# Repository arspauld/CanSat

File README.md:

## Welcome to GitHub Pages

You can use the [editor on GitHub](https://github.com/arspauld/CanSat/edit/master/README.md) to maintain and preview the content for your website in Markdown files.

Whenever you commit to this repository, GitHub Pages will run [Jekyll](https://jekyllrb.com/) to rebuild the pages in your site, from the content in your Markdown files.

### Markdown

Markdown is a lightweight and easy-to-use syntax for styling your writing. It includes conventions for

```markdown
Syntax highlighted code block

# Header 1
## Header 2
### Header 3

- Bulleted
- List

1. Numbered
2. List

**Bold** and _Italic_ and `Code` text

[Link](url) and 
```

For more details see [GitHub Flavored Markdown](https://guides.github.com/features/mastering-markdown/).

### Jekyll Themes

Your Pages site will use the layout and styles from the Jekyll theme you have selected in your [repository settings](https://github.com/arspauld/CanSat/settings). The name of this theme is saved in the Jekyll `_config.yml` configuration file.

### Support or Contact

Having trouble with Pages? Check out our [documentation](https://help.github.com/categories/github-pages-basics/) or [contact support](https://github.com/contact) and we’ll help you sort it out.

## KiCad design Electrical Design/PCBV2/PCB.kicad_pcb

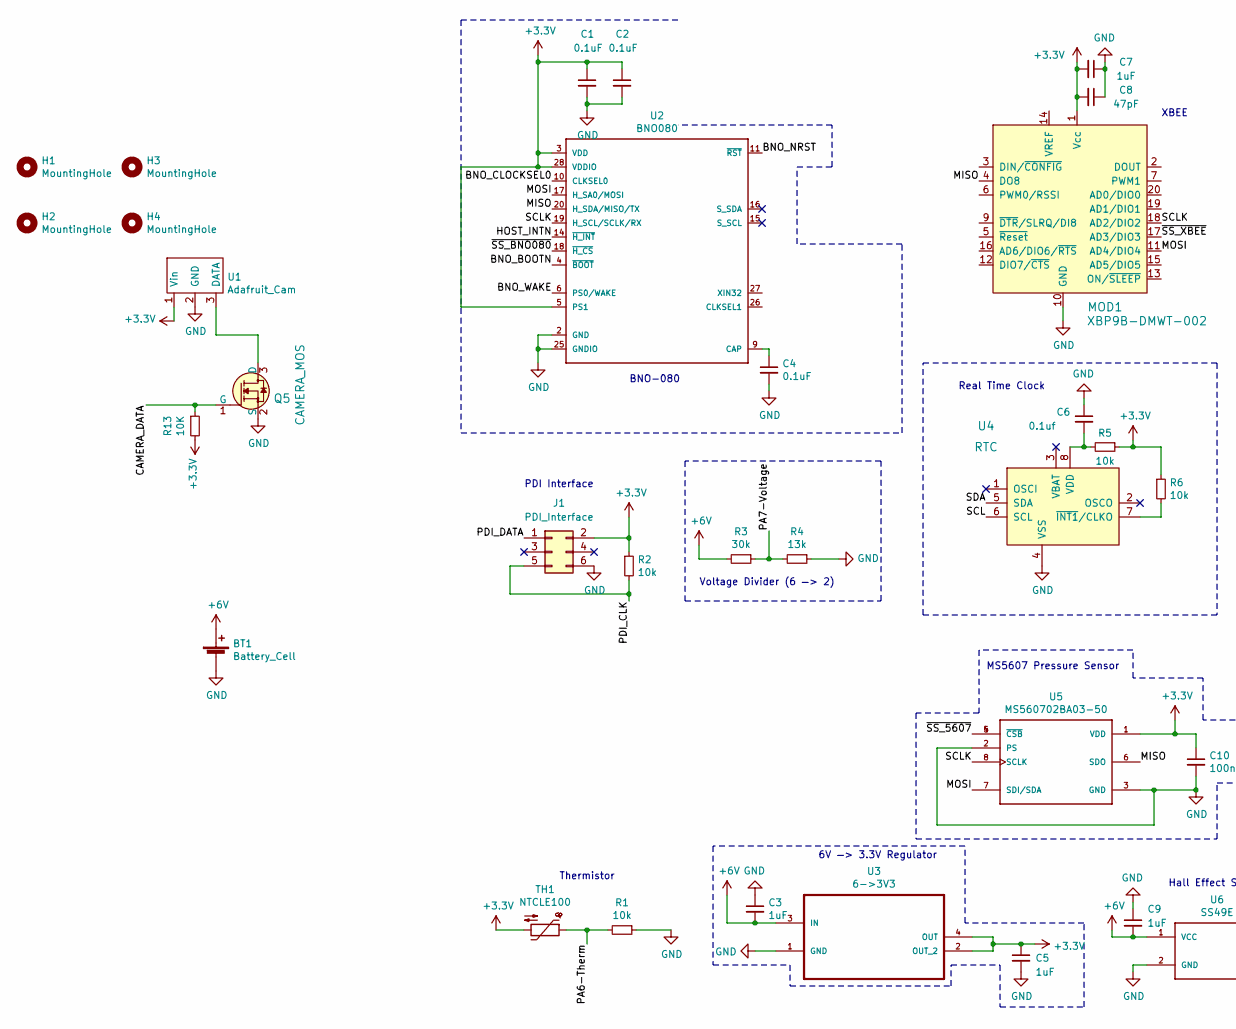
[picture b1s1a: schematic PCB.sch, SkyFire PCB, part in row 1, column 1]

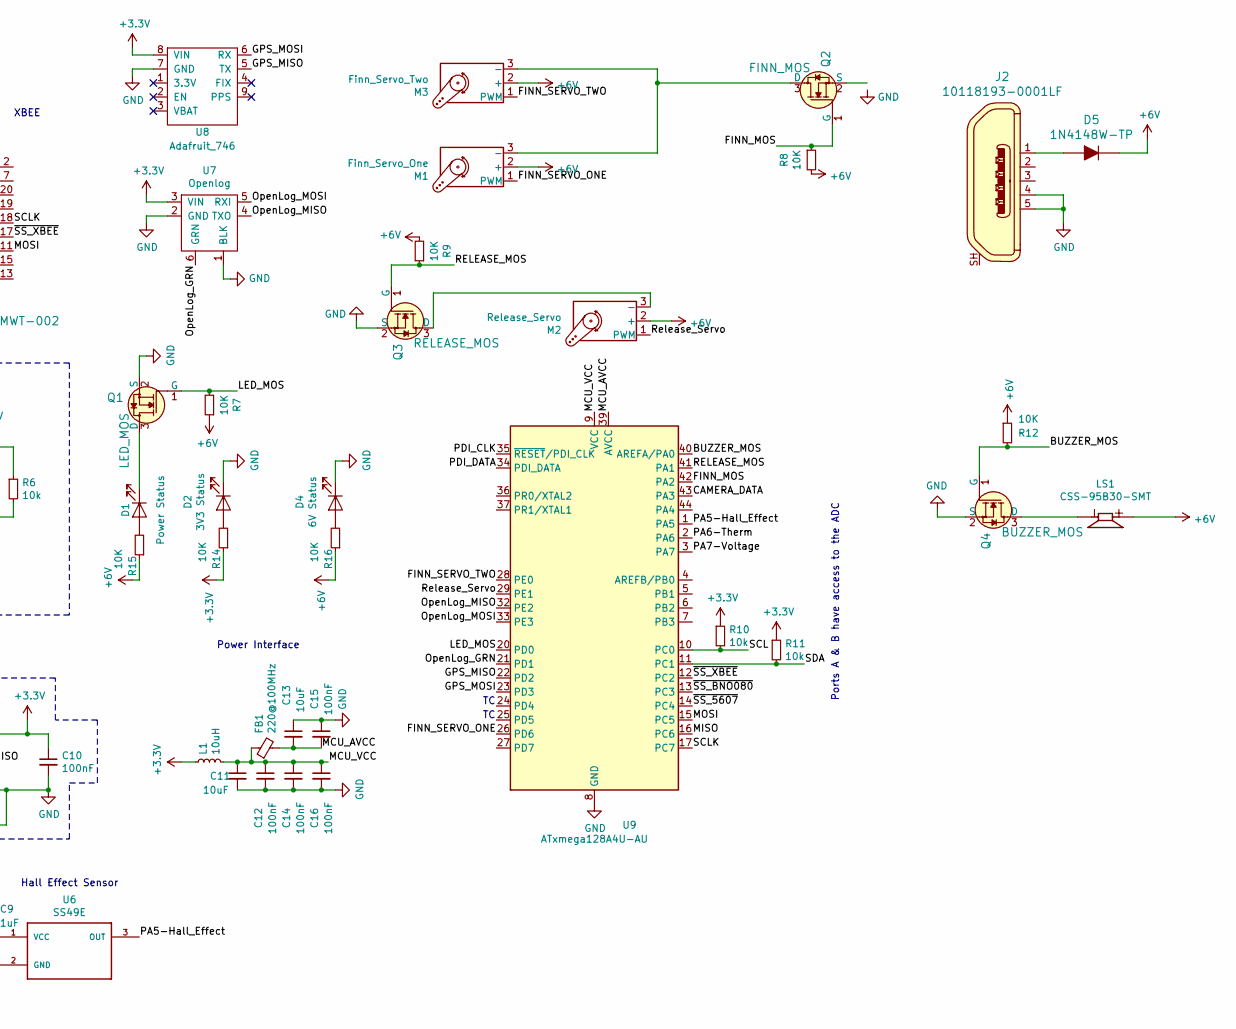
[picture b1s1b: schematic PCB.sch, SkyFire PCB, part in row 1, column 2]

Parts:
BT1: Battery_Cell; MOLEX-1X2_LOCK
C1, C2, C4: 0.1uF; C_0805_2012Metric_Pad1.15x1.40mm_HandSolder
C3, C5, C7, C9: 1uF; C_0805_2012Metric_Pad1.15x1.40mm_HandSolder
C6: 0.1uf; C_0805_2012Metric_Pad1.15x1.40mm_HandSolder
C8: 47pF; C_0805_2012Metric_Pad1.15x1.40mm_HandSolder
C10, C12, C14, C15, C16: 100nF; C_0805_2012Metric_Pad1.15x1.40mm_HandSolder
C11, C13: 10uF; C_0805_2012Metric_Pad1.15x1.40mm_HandSolder
D1: Power Status; LED_0603_1608Metric_Pad1.05x0.95mm_HandSolder
D2: 3V3 Status; LED_0603_1608Metric_Pad1.05x0.95mm_HandSolder
D4: 6V Status; LED_0603_1608Metric_Pad1.05x0.95mm_HandSolder
D5: 1N4148W-TP; SOD-123; MPN 1N4148W-TP; Digi-Key_PN 1N4148WTPMSCT-ND
FB1: 220@100MHz; L_0805_2012Metric_Pad1.15x1.40mm_HandSolder
H1, H2, H3, H4: MountingHole; MountingHole_3.2mm_M3
J1: PDI_Interface; 2X3
J2: 10118193-0001LF; USB_Micro_B_Female_10118193-0001LF; MPN 10118193-0001LF; Digi-Key_PN 609-4616-1-ND
L1: 10uH; L_0805_2012Metric_Pad1.15x1.40mm_HandSolder
LS1: CSS-95B30-SMT; CUI_CSS-95B30-SMT
M1: Finn_Servo_One; MOLEX-1X3_LOCK
M2: Release_Servo; MOLEX-1X3_LOCK
M3: Finn_Servo_Two; MOLEX-1X3_LOCK
MOD1: XBP9B-DMWT-002; XBEE_PRO-20_THT; MPN XBP9B-DMWT-002; Digi-Key_PN 602-1301-ND
Q1: LED_MOS; SOT-23-3; MPN 2N7002K-T1-E3; Digi-Key_PN 2N7002K-T1-E3CT-ND
Q2: FINN_MOS; SOT-23-3; MPN 2N7002K-T1-E3; Digi-Key_PN 2N7002K-T1-E3CT-ND
Q3: RELEASE_MOS; SOT-23-3; MPN 2N7002K-T1-E3; Digi-Key_PN 2N7002K-T1-E3CT-ND
Q4: BUZZER_MOS; SOT-23-3; MPN 2N7002K-T1-E3; Digi-Key_PN 2N7002K-T1-E3CT-ND
Q5: CAMERA_MOS; SOT-23-3; MPN 2N7002K-T1-E3; Digi-Key_PN 2N7002K-T1-E3CT-ND
R1, R2, R5, R6, R10, R11: 10k; R_0805_2012Metric_Pad1.15x1.40mm_HandSolder
R3: 30k; R_0805_2012Metric_Pad1.15x1.40mm_HandSolder
R4: 13k; R_0805_2012Metric_Pad1.15x1.40mm_HandSolder
R7, R8, R9, R12, R13, R14, R15, R16: 10K; R_0805_2012Metric_Pad1.15x1.40mm_HandSolder
TH1: NTCLE100; CP_Radial_D4.0mm_P1.50mm
U1: Adafruit_Cam; MOLEX-1X3_LOCK
U2: BNO080; LGA-28
U3: 6->3V3; SOT230P700X180-4N
U4: RTC; SOIC-8_W3.9mm; MPN PCF8523T/1,118; Digi-Key_PN 568-5306-1-ND
U5: MS560702BA03-50; SON125P300X500X100-8N
U6: SS49E; MOLEX-1X3_LOCK
U7: Openlog; 1X06
U8: Adafruit_746; 1X09
U9: ATxmega128A4U-AU; TQFP-44_10x10mm_P0.8mm

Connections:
+3V3: C1.1, C2.1, C5.1, C7.2, C8.2, C10.1, J1.2, L1.1, MOD1.1 (Vcc), R2.1, R5.1, R6.1, R10.1, R11.1, R13.2, R14.1, TH1.2, U1.1 (Vin), U2.3 (VDD), U2.5 (PS1), U2.28 (VDDIO), U3.2 (OUT_2), U3.4 (OUT), U5.1 (VDD), U7.3 (VIN), U8.8 (VIN)
+6V: BT1.1 (+), C3.2, C9.2, D5.K, LS1.P, M1.2 (+), M2.2 (+), M3.2 (+), R3.2, R7.1, R8.2, R9.2, R12.1, R15.1, R16.1, U3.3 (IN), U6.1 (VCC)
/BNO_BOOTN: U2.4 (~BOOT~)
/BNO_CLOCKSEL0: U2.10 (CLKSEL0)
/BNO_NRST: U2.11 (~RST~)
/BNO_WAKE: U2.6 (PS0/WAKE)
/BUZZER_MOS: Q4.1 (G), R12.2, U9.40 (AREFA/PA0)
/CAMERA_DATA: Q5.1 (G), R13.1, U9.43 (PA3)
/FINN_MOS: Q2.1 (G), R8.1, U9.42 (PA2)
/FINN_SERVO_ONE: M1.1 (PWM), U9.26 (PD6)
/FINN_SERVO_TWO: M3.1 (PWM), U9.28 (PE0)
/GPS_MISO: U8.5 (TX), U9.22 (PD2)
/GPS_MOSI: U8.6 (RX), U9.23 (PD3)
/HOST_INTN: U2.14 (~H_INT~)
/LED_MOS: Q1.1 (G), R7.2, U9.20 (PD0)
/MCU_AVCC: C13.2, C15.2, FB1.2, U9.39 (AVCC)
/MCU_VCC: C11.1, C12.1, C14.1, C16.1, FB1.1, L1.2, U9.9 (VCC), U9.19 (VCC), U9.31 (VCC)
/MISO: MOD1.4 (DO8), U2.20 (H_SDA/MISO/TX), U5.6 (SDO), U9.16 (PC6)
/MOSI: MOD1.11 (AD4/DIO4), U2.17 (H_SA0/MOSI), U5.7 (SDI/SDA), U9.15 (PC5)
/OpenLog_GRN: U7.6 (GRN), U9.21 (PD1)
/OpenLog_MISO: U7.4 (TXO), U9.32 (PE2)
/OpenLog_MOSI: U7.5 (RXI), U9.33 (PE3)
/PA5-Hall_Effect: U6.3 (OUT), U9.1 (PA5)
/PA6-Therm: R1.2, TH1.1, U9.2 (PA6)
/PA7-Voltage: R3.1, R4.2, U9.3 (PA7)
/PDI_CLK: J1.5, R2.2, U9.35 (~RESET~/PDI_CLK)
/PDI_DATA: J1.1, U9.34 (PDI_DATA)
/RELEASE_MOS: Q3.1 (G), R9.1, U9.41 (PA1)
/Release_Servo: M2.1 (PWM), U9.29 (PE1)
/SCL: R10.2, U4.6 (SCL), U9.10 (PC0)
/SCLK: MOD1.18 (AD2/DIO2), U2.19 (H_SCL/SCLK/RX), U5.8 (SCLK), U9.17 (PC7)
/SDA: R11.2, U4.5 (SDA), U9.11 (PC1)
/~SS_5607: U5.4 (~CSB~), U5.5 (~CSB~), U9.14 (PC4)
/~SS_BNO080: U2.18 (~H_CS~), U9.13 (PC3)
/~SS_XBEE: MOD1.17 (AD3/DIO3), U9.12 (PC2)
GND: BT1.2 (-), C1.2, C2.2, C3.1, C4.2, C5.2, C6.1, C7.1, C8.1, C9.1, C10.2, C11.2, C12.2, C13.1, C14.2, C15.1, C16.2, D2.1 (K), D4.1 (K), J1.6, J2.4, J2.5, MOD1.10 (GND), Q1.2 (S), Q3.2 (S), Q4.2 (S), Q5.2 (S), R1.1, R4.1, U1.2 (GND), U2.2 (GND), U2.25 (GNDIO), U3.1 (GND), U4.4 (VSS), U5.2 (PS), U5.3 (GND), U6.2 (GND), U7.1 (BLK), U7.2 (GND), U8.7 (GND), U9.8 (GND), U9.18 (GND), U9.30 (GND), U9.38 (GND)
unnamed: C4.1, U2.9 (CAP)
unnamed: C6.2, R5.2, U4.8 (VDD)
unnamed: D1.1 (K), Q1.3 (D)
unnamed: D1.2 (A), R15.2
unnamed: D2.2 (A), R14.2
unnamed: D4.2 (A), R16.2
unnamed: D5.A, J2.1
unnamed: LS1.N, Q4.3 (D)
unnamed: M1.3 (-), M3.3 (-), Q2.3 (D)
unnamed: M2.3 (-), Q3.3 (D)
unnamed: Q5.3 (D), U1.3 (DATA)
unnamed: R6.2, U4.7 (~INT1~/CLKO)

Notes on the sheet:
Ports A & B have access to the ADC
Voltage Divider (6 —> 2)
MS5607 Pressure Sensor
Power Interface
Hall Effect Sensor
6V —> 3.3V Regulator
PDI Interface
BNO-080
Thermistor
Real Time Clock
XBEE

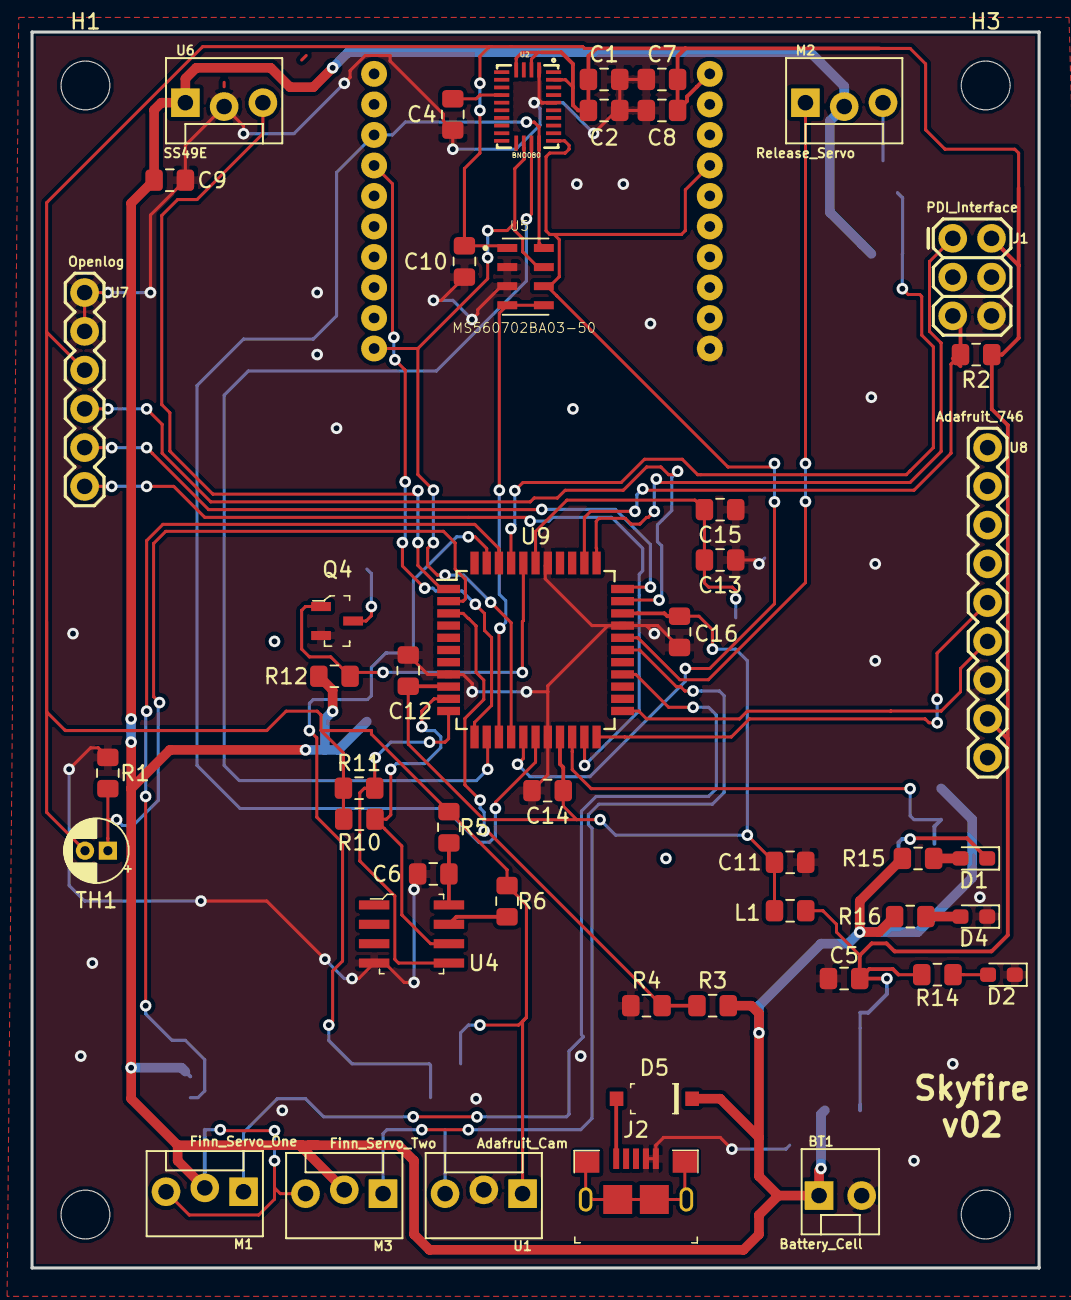
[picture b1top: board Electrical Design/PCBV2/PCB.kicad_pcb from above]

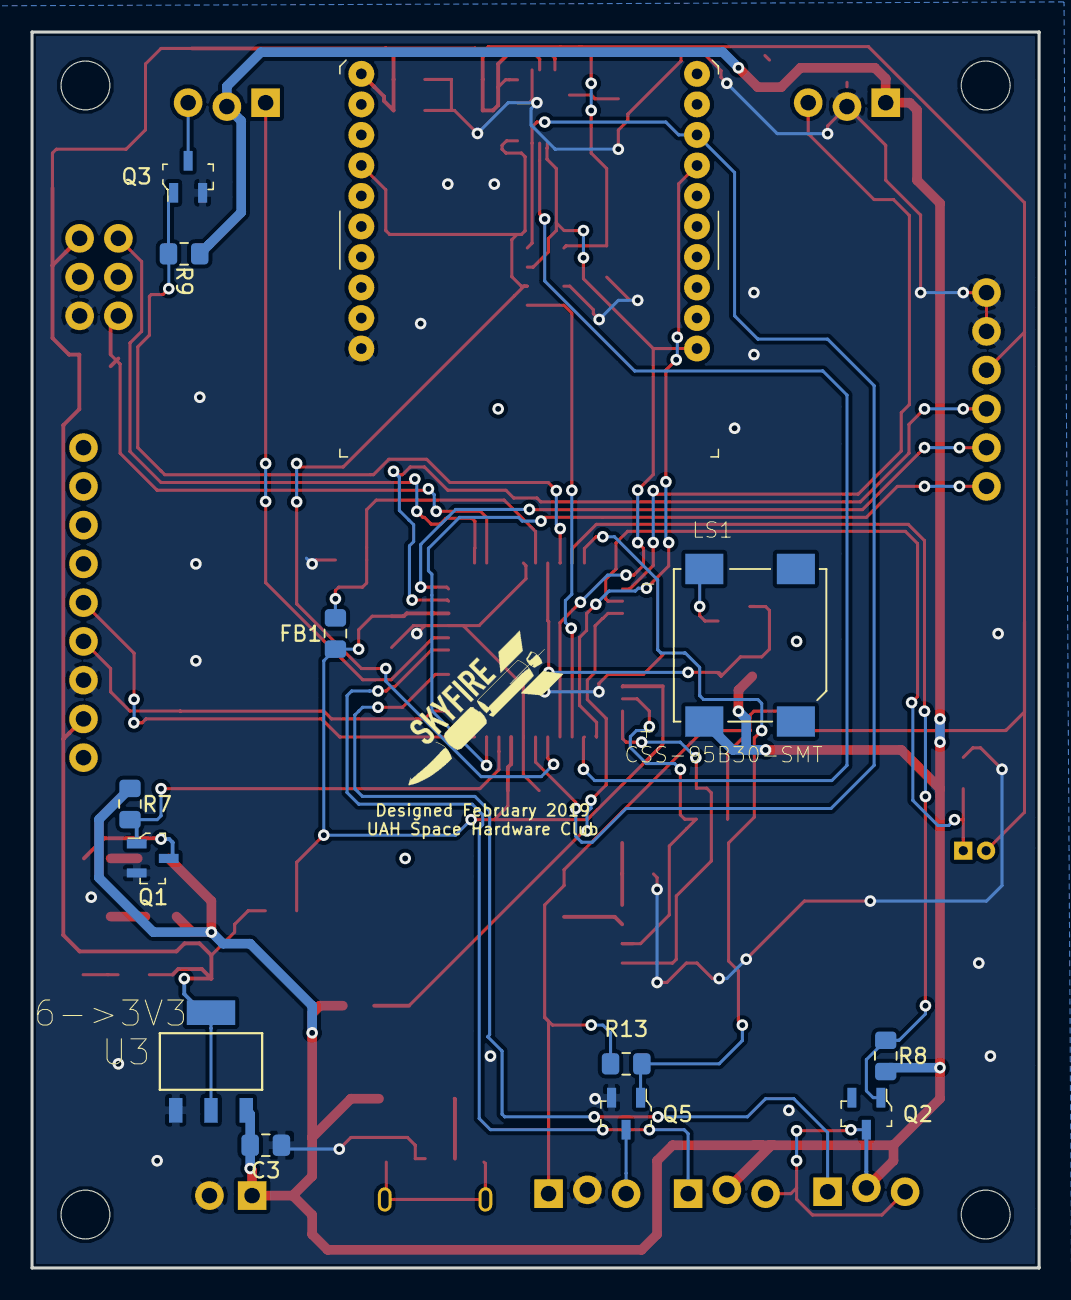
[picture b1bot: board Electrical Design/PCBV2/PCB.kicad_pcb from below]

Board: 2 copper layers, 66.0 x 81.0 mm, 65 parts (13 on the bottom side), 43 nets.

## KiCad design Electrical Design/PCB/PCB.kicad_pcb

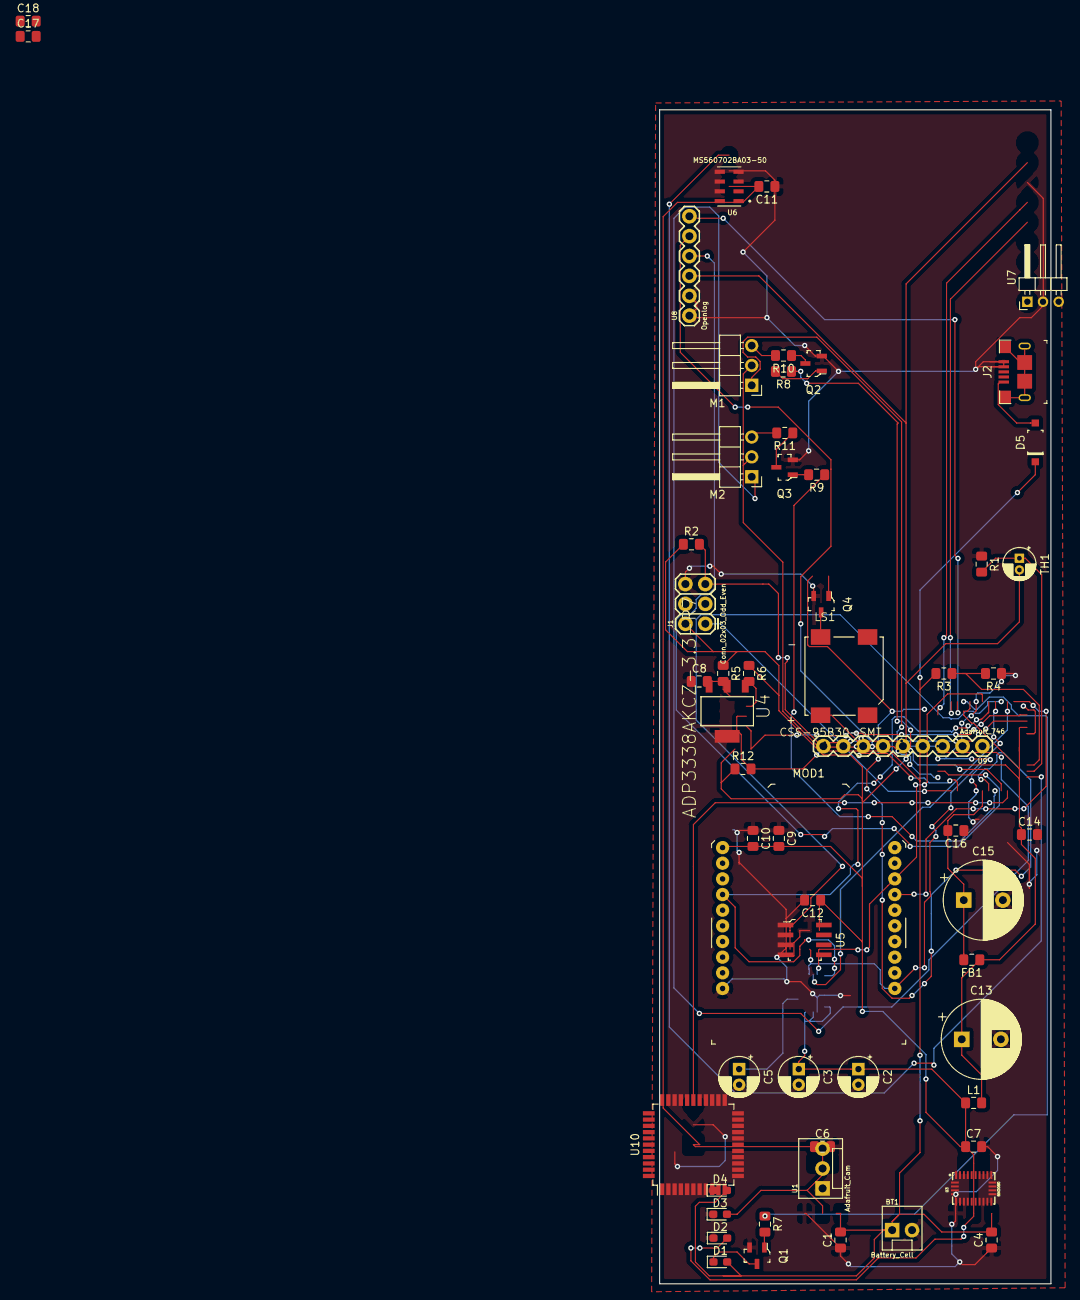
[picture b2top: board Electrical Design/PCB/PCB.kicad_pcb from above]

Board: 2 copper layers, 50.0 x 150.0 mm, 59 parts (1 on the bottom side), 43 nets.

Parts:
BT1: Battery_Cell; MOLEX-1X2
C1, C4, C6, C7, C9, C11: 1uF; C_0805_2012Metric_Pad1.15x1.40mm_HandSolder
C2, C3, C5: 0.1uF; CP_Radial_D5.0mm_P2.00mm
C8: 0.1uf; C_0805_2012Metric_Pad1.15x1.40mm_HandSolder
C10: 47pF; C_0805_2012Metric_Pad1.15x1.40mm_HandSolder
C12, C14, C16, C17, C18: 100nF; C_0805_2012Metric_Pad1.15x1.40mm_HandSolder
C13, C15: 10uF; CP_Radial_D10.0mm_P5.00mm
D1: Power Status; LED_0603_1608Metric_Pad1.05x0.95mm_HandSolder
D2: 3V3 Status; LED_0603_1608Metric_Pad1.05x0.95mm_HandSolder
D3: 5V Status; LED_0603_1608Metric_Pad1.05x0.95mm_HandSolder
D4: 6V Status; LED_0603_1608Metric_Pad1.05x0.95mm_HandSolder
D5: 1N4148W-TP; SOD-123
FB1: 220@100MHz; L_0805_2012Metric_Pad1.15x1.40mm_HandSolder
J1: Conn_02x03_Odd_Even; 2X3
J2: 10118193-0001LF; USB_Micro_B_Female_10118193-0001LF
L1: 10uH; L_0805_2012Metric_Pad1.15x1.40mm_HandSolder
LS1: CSS-95B30-SMT; CUI_CSS-95B30-SMT
M1: Camera_Servo; PinHeader_1x03_P2.54mm_Horizontal
M2: Release_Servo; PinHeader_1x03_P2.54mm_Horizontal
MOD1: XBP9B-DMWT-002; XBEE_PRO-20_THT
Q1: LED_MOS; SOT-23-3
Q2: CAMERA_MOS; SOT-23-3
Q3: RELEASE_MOS; SOT-23-3
Q4: BUZZER_MOS; SOT-23-3
R1, R2, R5, R6, R10, R11: 10k; R_0805_2012Metric_Pad1.15x1.40mm_HandSolder
R3: 30k; R_0805_2012Metric_Pad1.15x1.40mm_HandSolder
R4: 13k; R_0805_2012Metric_Pad1.15x1.40mm_HandSolder
R7, R8, R9, R12: 10K; R_0805_2012Metric_Pad1.15x1.40mm_HandSolder
TH1: NTCLE100; CP_Radial_D4.0mm_P1.50mm
U1: Adafruit_Cam; MOLEX-1X3
U2: ADP3338AKCZ-5-R7; SOT230P700X180-4N
U3: BNO080; LGA-28
U4: ADP3338AKCZ-3.3-R7; SOT230P700X180-4N
U5: PCF8523T_1_118; SOIC-8_W3.9mm
U6: MS560702BA03-50; SON125P300X500X100-8N
U7: SS495A; PinHeader_1x03_P2.00mm_Horizontal
U8: Openlog; 1X06
U9: Adafruit_746; 1X09
U10: ATxmega128A4U-AU; TQFP-44_10x10mm_P0.8mm

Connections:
+3V3: C2.1, C3.1, C7.1, C9.2, C10.2, C12.1, D2.2, J1.2, L1.1, MOD1.1, R2.1, R5.1, R6.1, R10.1, R11.1, TH1.2, U3.3, U3.5, U3.28, U4.2, U4.4, U6.1, U8.3, U9.8
+5V: C6.1, C11.2, D3.2, U1.1, U2.2, U2.4, U7.1
+6V: BT1.1, C1.2, C4.2, D1.2, D4.2, D5.K, LS1.P, M1.2, M2.2, R3.2, U2.3, U4.3
/BUZZER_MOS: R12.1, U10.40
/CAMERA_DATA: U1.3, U10.43
/CAMERA_MOS: R8.1, U10.42
/Camera_Servo: M1.1, U10.28
/GPS_MISO: U9.5, U10.22
/GPS_MOSI: U9.6, U10.23
/LED_MOS: R7.1, U10.20
/MCU_AVCC: C15.1, C17.2, FB1.2, U10.39
/MCU_VCC: C13.1, C14.1, C16.1, C18.1, FB1.1, L1.2, U10.9, U10.19, U10.31
/MISO: MOD1.4, U3.20, U6.6, U10.16
/MOSI: MOD1.11, U3.17, U6.7, U10.15
/OpenLog_GRN: U8.6, U10.21
/OpenLog_MISO: U8.4, U10.32
/OpenLog_MOSI: U8.5, U10.33
/PA5-Hall_Effect: U7.3, U10.1
/PA6-Therm: R1.2, TH1.1, U10.2
/PA7-Voltage: R3.1, R4.2, U10.3
/PDI_CLK: J1.5, R2.2, U10.35
/PDI_DATA: J1.1, U10.34
/RELEASE_MOS: R9.1, U10.41
/Release_Servo: M2.1, U10.29
/SCL: R10.2, U5.6, U10.10
/SCLK: MOD1.18, U3.19, U6.8, U10.17
/SDA: R11.2, U5.5, U10.11
/~SS_5607: U6.4, U6.5, U10.14
/~SS_BNO080: U3.18, U10.13
/~SS_XBEE: MOD1.17, U10.12
GND: BT1.2, C1.1, C2.2, C3.2, C4.1, C5.2, C6.2, C7.2, C8.1, C9.1, C10.1, C11.1, C12.2, C13.2, C14.2, C15.2, C16.2, C17.1, C18.2, D2.1, D3.1, D4.1, J1.6, J2.4, J2.5, MOD1.10, Q1.2, Q2.2, Q3.2, Q4.2, R1.1, R4.1, U1.2, U2.1, U3.2, U3.25, U4.1, U5.4, U6.2, U6.3, U7.2, U8.1, U8.2, U9.7, U10.8, U10.18, U10.30, U10.38
unnamed: C5.1, U3.9
unnamed: C8.2, R5.2, U5.8
unnamed: D1.1, Q1.3
unnamed: D5.A, J2.1
unnamed: LS1.N, Q4.3
unnamed: M1.3, Q2.3
unnamed: M2.3, Q3.3
unnamed: Q1.1, R7.2
unnamed: Q2.1, R8.2
unnamed: Q3.1, R9.2
unnamed: Q4.1, R12.2
unnamed: R6.2, U5.7

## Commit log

2018-10-24 Set theme jekyll-theme-tactile
2018-10-24 Set theme jekyll-theme-cayman
2018-10-25 First Commits
2018-10-26 Test 2
2018-10-26 Add files
2018-11-11 Update Software/Graph.py
    basic graphing software
2018-11-11 Python Test Alex
2018-11-11 Update Software/Graph.py
    pat can't spell
2018-12-11 Working towards a class for realtime plotting
2018-12-11 Created a class for realtime graphing and code for a random test of rt
2018-12-11 Found a Dock object to help with the GUI
2018-12-11 Made changes from a Python COnsole to a List and push button.
2018-12-12 Voltage Regulator Datasheet
2018-12-12 Housekeeping
2018-12-12 Added datalogger symbol
    Changed .gitignore file to ignore .DS_Store files (changes to this file type prevented pulling/pushing from/to origin)
2018-12-13 Create Mechanical
2018-12-13 add mechanical folder
2018-12-13 Added tge datalogger to Custom Library, made a few changes to pin types
2018-12-13 Housekeeping - trying not to overflow the folder
2018-12-14 General notes on how the file structure works
2018-12-14 Rename README to 1_README
2018-12-14 Create 2_CHANGELOG-NOTES
2018-12-14 Rename 2_CHANGELOG-NOTES to 1.1_CHANGELOG-NOTES
2018-12-14 Update 1_README
2018-12-15 Added new release mechanism
2018-12-15 Update 1.1_CHANGELOG-NOTES
2018-12-15 Add some xmega files
2018-12-15 Implement power circuit
2018-12-15 Fixed little bug
2018-12-15 Added PDI interface for MCU (maybe)
2018-12-15 More design tweaking
2018-12-15 Start implementing MS5607 application circuit
2018-12-15 Implement AP3419 appliation circuit
2018-12-16 Added airfoil rotor part
    I just popped a model of the airfoil in to the main assembly for reference. I'll add it to the rotors later
2018-12-17 Update main.py
    Made an interactive interface using a random plotter and a push button
2018-12-18 Datasheep
2018-12-18 Update main.py
    Added comments (whoops)
2018-12-18 Grounded the xmega
2018-12-18 Update main.py
    Checke the Setup
2018-12-18 Fixed DATALOGGER pins
2018-12-18 Changed standoff part numbers
2018-12-23 Added reaction wheel and minor changes
2019-01-03 Just a bunch of .dat and .pts files
2019-01-03 Datasheets
2019-01-03 GUI update
    Improved the layout of the GUI to be closer to the final product. Forgive the comments, or lack, but it was just a repetition of old work.
2019-01-03 GUI Updates
2019-01-03 Added SS490 Hall effect symbol
2019-01-03 Update main.py
    Re-did some code so all graphs update
2019-01-06 Revert "Merge branch 'master' of https://github.com/arspauld/CanSat"
    This reverts commit bc53826c9e0eb044944db2bb0ee00b51452b93e5, reversing
    changes made to 81d7122374d882940c6ee23d8daad00bd2ded12f.
2019-01-06 Still trying to add airfoil to cad
2019-01-06 Created a Atmel project
2019-01-06 Changed colors for PDR
2019-01-06 opened fins and transparency
2019-01-07 Nothing big just color changes
2019-01-08 Fixed Main.py
2019-01-12 creo science payload release servo definition modified
    creo servo definition modified
2019-01-13 More misc model adjustments
    blah
2019-01-18 Great
2019-01-18 Hmm a fuckin lot
2019-01-23 Trashed dsgn models+ dual rotor export
2019-01-23 Electrical Overhaul
2019-01-23 Added new model
2019-01-23 Solidedge tabs
2019-01-23 hmmmmmmmm
2019-01-23 fasjgfkjFH
2019-01-23 Revert "fasjgfkjFH"
    This reverts commit b96720fae449464ffa4fcaa81186aff08d1970dc.
2019-01-23 airfoil stl
2019-01-23 tgfr
2019-01-23 hhff
2019-01-23 rotor changes
2019-01-23 Ditched design into step final
2019-01-23 old cad
2019-01-23 dgasd
2019-01-23 Rfdh
2019-01-23 some shit
2019-01-23 more shit
2019-01-23 fuuuuuuuuccckkkkk
2019-01-23 files
2019-01-23 old_asm
2019-01-23 ffffff
2019-01-23 Naca blade modeled in step!
2019-01-23 uodate
2019-01-23 stuff
2019-01-23 Container V2
2019-01-23 Container Done - kinch
2019-01-23 Separation Guiderods
2019-01-23 Add voltages
2019-01-23 CAMERA MOUNT ADDED
2019-01-23 Colored old cad
2019-01-24 Mostly finished cad
2019-01-24 container Servo mounts
2019-01-25 more stuff
2019-01-26 ffdf
2019-01-26 the Springs are janky
2019-01-26 Springsss
2019-01-26 descent rate calc
2019-01-27 Bunch o shit
2019-01-27 Final push for tonight??
2019-01-28 Still working
2019-01-30 batteey
2019-01-30 OLD REACTION WHEEL
2019-01-30 more reaxction wheel
2019-01-30 Matlab is kicking my ass
2019-01-30 Done!
2019-01-31 Container 2 Parts
2019-01-31 Crappy Container 2
2019-01-31 New container stuff
2019-02-01 container shit
2019-02-01 Container 2 shell constraints
2019-02-05 airfoil xsects
2019-02-05 Organized files
2019-02-06 Wing X section stls made
2019-02-06 more rotor stuffs
2019-02-07 Datalogger, GPS, Radio
2019-02-07 Schemat_Done?
2019-02-07 Forget the Fets
2019-02-07 Assign footprints
2019-02-07 Add a lot of libraries and footprints
2019-02-07 Update Pins
2019-02-07 Netlist
2019-02-07 Generated initial PCB from schematic
2019-02-07 Update Thermistor Footprint
2019-02-07 Spread Components
2019-02-07 Placement
2019-02-08 Batteries and Camera
2019-02-08 PCB Layout
2019-02-08 Fix Batteries
2019-02-08 Start routing
2019-02-08 Fix Connector
2019-02-08 Were making progress
2019-02-08 Progress baby
2019-02-08 I think its done, but holy shit its bad
2019-02-08 Its fuckin done
2019-02-12 second rotor set stls
2019-02-12 working on barometric formula
2019-02-12 update pcb
2019-02-12 Start PCB Rev02
2019-02-12 New PCB
2019-02-12 fix the libraries
2019-02-13 Layout and edge cuts
2019-02-13 Almost reading for altitude logging
2019-02-13 major revision progress
2019-02-13 Start tracing
2019-02-13 Finish v02
2019-02-13 change logo stuff
2019-02-13 Final changes
2019-02-15 bugfixes
2019-02-15 fix logo
2019-02-15 fix silk screen
2019-02-26 added stl for whole rotor
2019-02-28 cura file
2019-03-02 more mods
2019-03-07 getting more parts for printing
2019-03-07 Some more stuffs
2019-03-08 lh rotor added
2019-03-13 attachment plate
2019-03-25 adding the loop that updates the plots
2019-03-25 description change
2019-03-27 gaaah dang this gonna be a lot
2019-03-27 TRY AGAIN
2019-03-27 SHIIIIIIIIIIT
2019-03-27 MORE FUQ UPPS
2019-03-27 print stuffs
2019-03-27 Code Stuf
2019-03-27 Move Software Changes
2019-03-27 container top
2019-04-03 Trimmed rotor adapter
2019-04-04 Made the *Mirrored* rotor hub stronger
2019-04-04 didn't fully save my last one
2019-04-05 ROTOR_HUB_V2 created
    It's essentially the same part as before, with the same dimensions and such. No dowel holes, but otherwise functionally the same, just modeled in Solid Edge.
2019-04-06 Added stops in line with the cansat axis on the top blades(partially), and stops on the new(and old) rotor hubs.
    computer ran out of battery, so rotor adapters still need to be smoothed out and have the holes redone
2019-04-06 Code shit
2019-04-06 Made independent rotor hub
2019-04-06 NEW_ASSEMBLY
2019-04-07 fun things
    - created csv_creation.py
    - started adding commands to main.py
    - edited realplot.update to include the app in the function arguments
2019-04-07 Code is working now
2019-04-07 change file name of .csv
2019-04-08 Updated Velocity function
2019-04-08 Hopefully made a data checking function and changed print outs
2019-04-10 Software updates
2019-04-11 Redid the variable handling
2019-04-12 code and drop test stuff
2019-04-12 added state checks
2019-04-13 create xbee_comm.py
    basic functions of an xbee using the python library
2019-04-13 update the remote 64 bit address
2019-04-13 SOME CRAZY SHIT
2019-04-13 Xbee and GPS work
    IT WORKS!!!
2019-04-13 shit ton of xbee work
    lit fam
2019-04-14 STUF
2019-04-14 More development
2019-04-15 more code shit
2019-04-19 stuffs
2019-04-19 V2 hub adapter stl added
2019-04-19 battery lock update
2019-04-19 GCODE
2019-04-19 Servo arm V2
2019-04-19 code is on pcb, ms5607 is weird
2019-04-20 Load the board with this code
2019-05-04 Cotton Xbee trial
2019-05-04 Ground Station Development
2019-05-04 new design
2019-05-07 u frame stuff
2019-05-13 timer fix
2019-05-13 made new files and pid skeleton
2019-05-16 stl files added
    stl files
2019-05-16 Update Container Top V3 (Dimensions too large).par
    parachute bolt holes added
2019-05-17 fin stuffs
2019-05-17 added SD card protector piece
2019-05-17 Finished up ground station, cleaned up folder
2019-05-19 code shit
    gps now works and xbee is on spi, but doesn't work
2019-05-19 looked at assembly
2019-05-19 cotton, try this
2019-05-19 python -> exe
2019-05-20 CLEANING UP STUFF
    CAPSLOCK IS ON. OOPS
2019-05-21 lightening stuff
2019-05-21 more lightening
2019-05-22 finalization (hopefully)
2019-05-23 bno085 work
    this shit is crazy
2019-05-24 apparently duplicated files
2019-05-28 ROTOR LOCKS
    Might use these to keep rotors from folding up when landing
2019-05-29 more changes
2019-05-30 sometin else
2019-06-01 code update (don't compile)
2019-06-01 EEPROM and Compile
2019-06-02 XBEE on OpenLog Terminal
2019-06-02 Changes part 2
2019-06-02 solution change
2019-06-02 fixed data overload on GCS
2019-06-02 test flight data
2019-06-02 Successful run on One Month Board
    Pressure Sensor is fine
2019-06-02 confirmation using OneMonth board approved code
2019-06-02 THE EEPROM FUCKING WORKS MATES
2019-06-03 NEW HUB
2019-06-03 LANDING GEAR
2019-06-04 code updates, servos work
2019-06-04 CHeck Pressure Calc on other board
2019-06-04 LANDING GEAR READY
2019-06-04 READY TO PRINT
2019-06-04 Blade Redesign
    X-Cross Bars
2019-06-05 New hubs for Sign Board/ Redesign of Back PCB Case
2019-06-05 Code updates
    will test BNO
2019-06-05 Xbee
2019-06-06 Magnet rotor hole, signboard adapter correct dimensions
2019-06-06 Worked on Servos and buzzer
2019-06-06 PCB cases updated for 2 servo design
2019-06-06 updates to pcb_case v4 and assem v2
2019-06-06 dimension updates
2019-06-06 PCB Case Revisions
2019-06-06 DRONE MOTOR MOUNTS
2019-06-06 fin design partway done, increased magnet hole size to 7mm
2019-06-06 New Fins/Conectors
2019-06-06 DRONE MOTORS ARE BACK
2019-06-07 Software is buzzing
2019-06-07 updates tp signboard adapters
2019-06-08 updated release arm hole size/position
2019-06-08 more data
2019-06-08 New release Arm
2019-06-09 FILES JUMBLED TEST-- PUSHING FROM ZAC'S OLD LAPTOP
    Files that will need updating:
    ROTOR_HUB_V2_bottom
    Files that MiGhT need updating:
    everything???
2019-06-09 Work stuff
2019-06-09 Moved Folders because GitHub is a pain in the ass
2019-06-09 Recovered mechanical files
2019-06-09 deleted Science Payload
2019-06-10 flight state logic fixed
2019-06-10 Added servo_release command
2019-06-10 file organization
2019-06-10 Fixed the pressure sensor
2019-06-10 file updates/recovery, renaming continued. No new/modified files as far as I know
2019-06-10 added servo release command
2019-06-10 servo close command added
2019-06-10 flight state logic reworked
2019-06-10 Code work
2019-06-10 EEPROM inclusion in startup
2019-06-11 frequency for buzzer changed
2019-06-11 PWM was flipped
2019-06-11 updates PWM
2019-06-11 cleaned up main.py, edited README
2019-06-11 Made Test board
2019-06-11 EEPROM improvements
2019-06-11 hall effect sensor configured
2019-06-11 hall effect editing
2019-06-12 Hall Effect works!
2019-06-12 test flight
2019-06-12 hall effect hysteresis updated
2019-06-12 bullshit
2019-06-12 one month board code
2019-06-12 made it for our boards again
2019-06-12 shit
2019-06-12 basic sensors work
2019-06-12 continued work
2019-06-12 commenting
2019-06-12 im a big dumb so i fixed the adc
    rip
2019-06-12 VOLTAGE READER AND THERMISTOR WORK
2019-06-12 nice data yay
2019-06-12 fixed calibrate commands in GUI
2019-06-12 hall effect sensor working
2019-06-12 moved around conditionals and new flight data
2019-06-12 Stl updated
2019-06-12 Pressure sensor is up again
2019-06-12 flight state edits
2019-06-12 launch code
2019-06-13 flight calculations and slight edits
2019-06-14 PID is up, now for the camera
2019-06-14 environmental tests
2019-06-15 container top stl updated
2019-06-15 ground station editing
2019-06-15 Final Code changes
2019-06-15 Final Change
2019-06-15 Back up computer comms
2019-06-16 cansat final flight data
2019-06-19 We done bois
2019-07-26 add a comment
